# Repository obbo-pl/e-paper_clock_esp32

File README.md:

# e-paper_clock_esp32
e-paper clock with ESP32

##### Requirements: 
- ESP IDF 4.3.1
- LVGL 7.x
- LVGL driver uc8179c (https://github.com/obbo-pl/lvgl_esp32_drivers/tree/uc8179c)

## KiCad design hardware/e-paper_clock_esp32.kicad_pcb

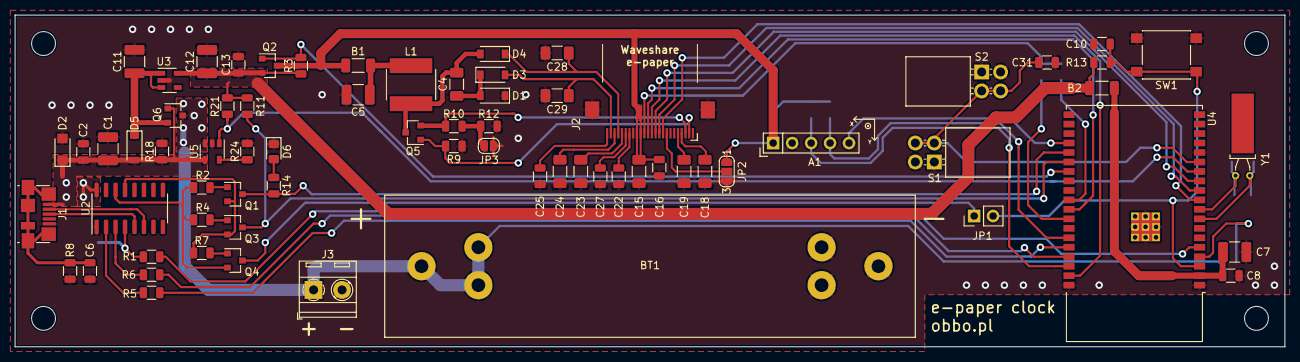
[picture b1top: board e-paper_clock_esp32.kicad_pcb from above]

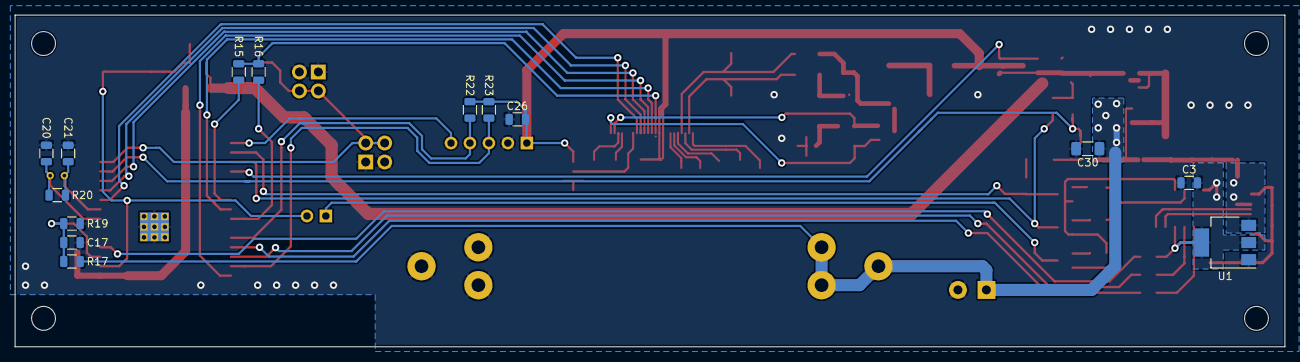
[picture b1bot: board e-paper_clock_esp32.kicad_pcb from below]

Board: 2 copper layers, 170.2 x 44.5 mm, 89 parts (14 on the bottom side), 60 nets.

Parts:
A1: SEN0168; DFROBOT_SEN0168
B1, B2: bead; L_1206_3216Metric_Pad1.22x1.90mm_HandSolder
BT1: Li-Ion; BatteryHolder_Keystone_KEYS54_18650
C1, C5, C11, C12: 10u; C_1210_3225Metric_Pad1.33x2.70mm_HandSolder
C2, C6, C8, C13, C16, C17, C26, C31: 100n; C_0805K
C3, C10, C22, C25: 1u; C_0805K
C4, C15, C19, C23, C24, C28, C29, C30: 4.7u; C_1206_3216Metric_Pad1.33x1.80mm_HandSolder
C7: 22u; C_1210_3225Metric_Pad1.33x2.70mm_HandSolder
C18: NP; C_1206_3216Metric_Pad1.33x1.80mm_HandSolder
C20, C21: 12p; C_0805K
C27: NP; C_0805K
D1, D3, D4, D5: MBR0530; D_SOD-123
D2: SMF5V0A-E3-08; D_SMF
D6: LED; LED_0805_2012Metric_Pad1.15x1.40mm_HandSolder
H1, H2, H3, H4: MountingHole; MountingHole_3.2mm_M3
J1: USB_B_Micro; USB_Micro-B_HandSoldering
J2: HIROSE FH12-24S-0.5SH-55; FFC_Hirose_FH12-24S-0.5SH
J3: Screw_Terminal_01x02; TerminalBlock_Degson_DG381-3.81-02P
JP1: Serial RTS; PinHeader_1x02_P2.54mm_Vertical
JP2: SPI Line; SolderJumper-3_P1.3mm_Open_RoundedPad1.0x1.5mm_NumberLabels
JP3: Current Sense; SolderJumper-2_P1.3mm_Open_RoundedPad1.0x1.5mm
L1: 10uH 1.9A 65mOhm; L_FerroCore_DJNR6045-S_HandSoldering
Q1, Q3, Q4: BC847; SOT-23
Q2, Q6: AO3401A; SOT-23
Q5: AO3400; SOT-23
R1: 620; R_0805K
R2, R3, R4, R7, R11, R13, R18, R21: 10k; R_0805K
R5, R6: 390; R_0805K
R8: 100k; R_0805K
R9: 1M; R_0805K
R10: 0.47; R_0805K
R12: 2.2; R_0805K
R14: 1k; R_0805K
R15: 1.8k; R_0805K
R16: 0; R_0805K
R17, R19, R20: 3.3M; R_0805K
R22, R23: 3.3k; R_0805K
R24: 2.2k; R_0805K
S1, S2: RBS070410; TiltSensorSwitch_RBS070410
SW1: RESET; SW_SPST_PTS645
U1: LD1117S33TR_SOT223; SOT-223-3_TabPin2
U2: CH340C; SOIC-16_3.9x9.9mm_P1.27mm
U3: AP2112K-3.3; SOT-23-5
U4: ESP32-WROVER-E
U5: MCP73832-2-OT; SOT-23-5
Y1: 32.768k; Crystal_C38-LF_D3.0mm_L8.0mm_Horizontal_1EP_style1

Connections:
+3V3: B2.1, C12.1, C13.1, Q2.2, R3.1, R11.1, R13.1, R21.1, U3.5
+BATT: BT1.1, C30.1, J3.1, Q6.3, R17.1, U5.3
/BATTERY_VOLTAGE: C17.1, R17.2, R19.1, U4.4
/MISO: R16.2, U4.31
/MOSI: R15.1, U4.29
BATTERY_CHARGE: R21.2, U4.13, U5.1
BS: J2.8, JP2.2
EPAPER_PWR: Q2.1, R3.2, U4.26
EP_BUSY: J2.9, U4.10
EP_CS: J2.12, U4.37
EP_DC: J2.11, U4.12
EP_RST: J2.10, U4.11
EP_SCLK: J2.13, U4.30
EP_SDI: J2.14, R15.2, R16.1
GDR: J2.2, Q5.1, R9.1
GND: A1.2, BT1.2, C1.2, C2.2, C3.2, C5.2, C6.2, C7.2, C8.2, C10.2, C11.2, C12.2, C13.2, C15.2, C16.2, C17.2, C18.2, C19.2, C20.2, C21.2, C22.2, C23.2, C24.2, C25.2, C26.2, C27.2, C28.2, C29.2, C30.2, C31.2, D1.1, D2.2, D6.1, J1.5, J2.17, J2.MP, J3.2, JP2.3, JP3.2, R8.2, R9.2, R12.2, R18.2, R19.2, R24.2, S1.1, S1.2, S2.1, S2.2, SW1.1, U1.1, U2.1, U3.2, U4.1, U4.15, U4.38, U4.39, U5.2
IO0: Q3.3, R11.2, U4.25
IO2: Q1.3, R14.2, U4.24
unnamed: B1.2, C5.1, L1.1
unnamed: B2.2, C7.1, C8.1, U4.2
unnamed: C3.1, R1.1, U1.2, U2.4, U2.16
unnamed: C4.1, D1.2, D3.1
unnamed: C4.2, D4.2, L1.2, Q5.3
unnamed: C6.1, J1.6, R8.1
unnamed: C11.1, D5.1, Q6.2, U3.1, U3.3
unnamed: C18.1, J2.4
unnamed: C19.1, J2.5
unnamed: C20.1, R20.2, U4.8, Y1.1
unnamed: C21.1, R20.1, U4.9, Y1.2
unnamed: C22.1, J2.18
unnamed: C23.1, J2.20
unnamed: C24.1, J2.22
unnamed: C25.1, J2.24
unnamed: C27.1, J2.19
unnamed: D6.2, R14.1
unnamed: J1.2, U2.6
unnamed: J1.3, U2.5
unnamed: JP1.1, Q4.3
unnamed: JP3.1, R10.2, R12.1
unnamed: Q1.1, R2.1
unnamed: Q1.2, Q3.2, R7.2, U2.13
unnamed: Q3.1, R4.1
unnamed: Q4.1, R7.1
unnamed: Q4.2, R2.2, R4.2, U2.14
unnamed: R5.1, U2.2
unnamed: R6.2, U2.3
unnamed: R24.1, U5.5
PREVGH: C28.1, D4.1, J2.21
PREVGL: C29.1, D3.2, J2.23
RESE: J2.3, Q5.2, R10.1
RST: C10.1, JP1.2, R13.2, SW1.2, U4.3
SCL: A1.3, R23.2, U4.36
SDA: A1.4, R22.2, U4.33
SEN0168_INT: A1.5, U4.23
SENSOR_TILT: C31.1, S1.3, S1.4, S2.3, S2.4, U4.14
USB-Rx: R6.1, U4.35
USB-Tx: R5.2, U4.34
VBUS: C1.1, C2.1, D2.1, D5.2, J1.1, Q6.1, R18.1, U1.3, U5.4
VBUS_VOLTAGE: R1.2, U4.5
VDD: A1.1, B1.1, C15.1, C16.1, C26.1, J2.15, J2.16, JP2.1, Q2.3, R22.1, R23.1

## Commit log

2022-07-24 Requirements
2022-11-05 interrupt configuration
2022-11-06 tilt and shake detection
2022-11-11 added "tilt back" action
2023-04-30 top view
